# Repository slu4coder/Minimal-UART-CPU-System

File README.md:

# Legacy: Minimal UART CPU System

See https://github.com/slu4coder/Minimal-64x4-Home-Computer for the most recent version.

Quick note: This is a free and non-commercial project. I am in no way associated with any activies selling this as a product.
Any such activity represents a license violation. Individual licenses apply for hardware and software parts. Please refer to
appropriate documentations for detailed licensing information.

Minimal CPU 2.0 'Ultra' is now running at 10MHz(!) and may well be the fastest 8-bit general purpose 74HC logic breadboard computer to this date:

Latest PCB version 1.5:

● Build your own 'Minimal CPU System' on breadboards: https://www.youtube.com/watch?v=Gz1VVOsNn_8

● Python-like high-level programming language MIN released: https://www.youtube.com/watch?v=H342TwW4R7k

● 'Minimal VGA Extension Card' released! https://github.com/slu4coder/DIY-VideoRAM/tree/main/KiCAD

● 'Minimal CPU System' Emulator released! See user manual chapter 'Minimal Emulator' for details.

● Native assembler and text editor released!

● User Manual and Reference: https://docs.google.com/document/d/1c2ZHtLd1BBAwcBAjBZZJmCA3AXpbpv80dlAtsMYpuF4/edit?usp=sharing

● Revision 1.5 is out now featuring 512KB FLASH SSD, 3.6864MHz clock speed and an expansion port!
https://www.youtube.com/watch?v=osVi06VKvA0

● Minimal Python Assembler released: https://www.youtube.com/watch?v=rdKX9hzA2lU

● The Minimal CPU System now has a dedicated hardware serial 'Minimal Terminal': https://github.com/slu4coder/Minimal-Terminal
but can also be operated via a USB-to-serial breakout board and a terminal emulation (e. g. Tera Term) of cause.

I've built my own Computer from scratch - using nothing but TTL chips, because, well, why not? I wanted a CPU that is easy to understand, fun to build and powerful enough to allow for programming educational stuff and little games on it. Ah, and by the way - it should be as simple as possible - sort of the "Simplest Usable Personal Computer". This repo provides you with everything you need to follow my one-and-a-half-year journey down this rabbit hole. Besides running some video game classics, this little DIY CPU is capable of parsing arbitrary mathmatical expressions and performing floating point calculations in single (32-bit) precision. And it comes with an SSD file system, too, since it uses it's own FLASH IC as permanent SSD storage. Over the last year I have written an entire native toolchain: a text editor, an assembler and the Python-like high-level programming language MIN.

WHAT YOU GET:

  ● Block diagram of the CPU and overview it's instruction set
  
  ● KiCAD project files with detailed schematics and PCB layout
  
  ● Gerber files ready to be submitted at any PCB manufacturer of your choice
  
  ● Bill of material
  
  ● Images in .bin format of both the ROM and the CPU's control microcode
  
  ● Source code of the minimal operating system MinOS and several demos and games
  
  ● Cross-assembler 'asm.exe' running on Windows (or Python) to comfortably write, assemble and upload your own software

TECHNICAL SPECIFICATION:
  
  ● Processing power (1.0Mips @8.3MHz) comparable to 2.3 x Commodore 64 or Apple II
  
  ● Clear(est?) and simple(st? – you judge!) design for fun and education
  
  ● 8-bit data bus, 16-bit address bus, Von-Neumann architecture
  
  ● 64 instructions (conditional branching, subroutines, stack and word ops)
  
  ● 32KB RAM / 512KB FLASH ROM (OS, memory monitor, disassembler, tools)
  
  ● SSD file system (commands LOAD, SAVE, DIR, DELETE, FORMAT as you'd expect)
  
  ● UART interface (up to 500kbps) for terminal display, keyboard input and file I/O
 
  ● Expansion port (I/O card and VGA card available, build your own!)
   
  ● 24 (16) control signals, 2 registers A and B, ALU (arithmetic and logic unit) = simple adder, 3 flags (negative, carry and zero)
  
  ● Built from 74HCxx TTL logic on 120mm x 190mm PCB or 8 breadboards

I hope you find this information useful, educational or otherwise interesting. I'd love to hear about your build, so meet me on YouTube.

https://www.youtube.com/channel/UCXYQcMpUBT3aaQKfmAVJNow

Have fun!
slu4

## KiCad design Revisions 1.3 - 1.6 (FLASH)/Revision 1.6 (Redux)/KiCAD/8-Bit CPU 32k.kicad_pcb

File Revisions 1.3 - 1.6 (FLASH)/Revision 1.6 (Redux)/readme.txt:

Revision 1.6 ("Redux") is software-compatible to revision 1.5. The schematics and the microcode, however, have been optimized for build-simplicity on breadboards. Only 39 ICs are being used, compared to the 47 ICs of revision 1.5.

NEW: Minimal 'Beast Mode' can run at up to 8.3MHz clock speed.

ONLY USE HIGH-QUALITY BREADBOARDS FOR YOUR BUILD!

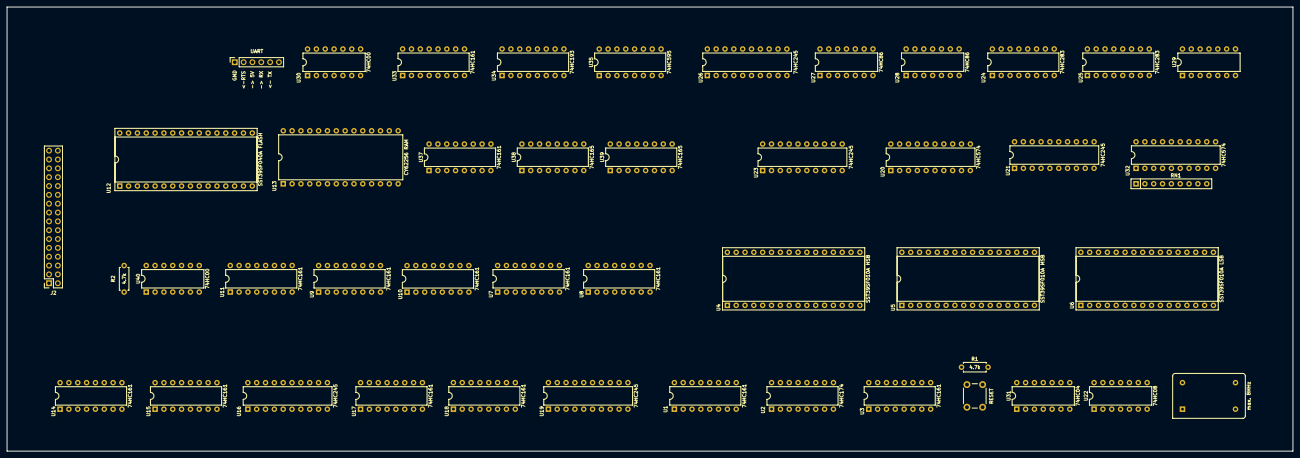
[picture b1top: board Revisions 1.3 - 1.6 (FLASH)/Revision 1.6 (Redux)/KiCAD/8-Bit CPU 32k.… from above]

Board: 2 copper layers, 369.6 x 127.6 mm, 46 parts (0 on the bottom side), 150 nets, no tracks yet.

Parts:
J1: UART; PinSocket_1x06_P2.54mm_Vertical
J2: EXPANSION PORT; PinSocket_2x16_P2.54mm_Vertical
R1, R2: 4.7k; R_Axial_DIN0207_L6.3mm_D2.5mm_P7.62mm_Horizontal
RN1: 470; R_Array_SIP9
SW1: RESET; SW_PUSH_6mm
U1, U3, U7, U8, U9, U10, U11, U14, U15, U17, U18, U33, U37: 74HC161; DIP-16_W7.62mm
U2: 74HC174; DIP-16_W7.62mm
U4: SST39SF010A HSB; DIP-32_W15.24mm_Socket
U5: SST39SF010A MSB; DIP-32_W15.24mm_Socket
U6: SST39SF010A LSB; DIP-32_W15.24mm_Socket
U12: SST39SF040A FLASH; DIP-32_W15.24mm_Socket
U13: CY62256 RAM; DIP-28_W15.24mm
U16, U19, U21, U23, U26: 74HC245; DIP-20_W7.62mm
U20, U32: 74HC574; DIP-20_W7.62mm
U22: 74HC08; DIP-14_W7.62mm
U24, U25: 74HC283; DIP-16_W7.62mm
U27, U28: 74HC86; DIP-14_W7.62mm
U29: 74HC4078; DIP-14_W7.62mm
U30, U40: 74HC00; DIP-14_W7.62mm
U31: 74HC04; DIP-14_W7.62mm
U34: 74HC193; DIP-16_W7.62mm
U35: 74HC595; DIP-16_W7.62mm
U38, U39: 74HC165; DIP-16_W7.62mm
X1: max. 8MHz; Oscillator_DIP-14

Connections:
+5V: J1.3, J2.3, R1.1, R2.2, RN1.1 (common), U1.1 (~MR), U1.16 (VCC), U2.1 (~Mr), U2.16 (VCC), U3.7 (CEP), U3.10 (CET), U3.16 (VCC), U4.31 (~WE), U4.32 (VCC), U5.31 (~WE), U5.32 (VCC), U6.31 (~WE), U6.32 (VCC), U7.1 (~MR), U7.16 (VCC), U8.1 (~MR), U8.16 (VCC), U9.1 (~MR), U9.16 (VCC), U10.1 (~MR), U10.16 (VCC), U11.16 (VCC), U12.32 (VCC), U13.28 (VCC), U14.16 (VCC), U15.16 (VCC), U16.20 (VCC), U17.16 (VCC), U18.16 (VCC), U19.20 (VCC), U20.20 (VCC), U21.20 (VCC), U22.14 (VCC), U23.20 (VCC), U24.16 (VCC), U25.16 (VCC), U26.20 (VCC), U27.14 (VCC), U28.14 (VCC), U29.7 (GND), U30.14 (VCC), U31.14 (VCC), U32.20 (VCC), U33.7 (CEP), U33.9 (~PE), U33.16 (VCC), U34.1 (D1), U34.5 (CPU), U34.9 (D3), U34.16 (VCC), U35.10 (~SRCLR), U35.16 (VCC), U37.7 (CEP), U37.9 (~PE), U37.10 (CET), U37.16 (VCC), U38.6 (D7), U38.16 (VCC), U39.3 (D4), U39.4 (D5), U39.10 (DS), U39.11 (D0), U39.12 (D1), U39.13 (D2), U39.14 (D3), U39.16 (VCC), U40.14 (VCC), X1.14 (Vcc)
/ALU/A0: U21.18 (B0), U24.5 (A1), U32.19 (Q0)
/ALU/A1: U21.17 (B1), U24.3 (A2), U32.18 (Q1)
/ALU/A2: U21.16 (B2), U24.14 (A3), U32.17 (Q2)
/ALU/A3: U21.15 (B3), U24.12 (A4), U32.16 (Q3)
/ALU/A4: U21.14 (B4), U25.5 (A1), U32.15 (Q4)
/ALU/A5: U21.13 (B5), U25.3 (A2), U32.14 (Q5)
/ALU/A6: U21.12 (B6), U25.14 (A3), U32.13 (Q6)
/ALU/A7: U21.11 (B7), U25.12 (A4), U32.12 (Q7)
/ALU/B0: U20.19 (Q0), U23.18 (B0), U27.13
/ALU/B1: U20.18 (Q1), U23.17 (B1), U27.10
/ALU/B2: U20.17 (Q2), U23.16 (B2), U27.2
/ALU/B3: U20.16 (Q3), U23.15 (B3), U27.5
/ALU/B4: U20.15 (Q4), U23.14 (B4), U28.13
/ALU/B5: U20.14 (Q5), U23.13 (B5), U28.10
/ALU/B6: U20.13 (Q6), U23.12 (B6), U28.2
/ALU/B7: U20.12 (Q7), U23.11 (B7), U28.5
/ALU/BUS0: J2.9, RN1.2 (R1), U2.3 (D0), U7.3 (D0), U9.3 (D0), U11.3 (D0), U12.13 (I/O0), U13.11 (I/O0), U14.3 (D0), U16.2 (A0), U17.3 (D0), U19.2 (A0), U20.2 (D0), U21.2 (A0), U23.2 (A0), U26.2 (A0), U32.2 (D0), U35.7 (QH), U38.4 (D5)
/ALU/BUS1: J2.10, RN1.3 (R2), U2.4 (D1), U7.4 (D1), U9.4 (D1), U11.4 (D1), U12.14 (I/O1), U13.12 (I/O1), U14.4 (D1), U16.3 (A1), U17.4 (D1), U19.3 (A1), U20.3 (D1), U21.3 (A1), U23.3 (A1), U26.3 (A1), U32.3 (D1), U35.6 (QG), U38.3 (D4)
/ALU/BUS2: J2.11, RN1.4 (R3), U2.6 (D2), U7.5 (D2), U9.5 (D2), U11.5 (D2), U12.15 (I/O2), U13.13 (I/O2), U14.5 (D2), U16.4 (A2), U17.5 (D2), U19.4 (A2), U20.4 (D2), U21.4 (A2), U23.4 (A2), U26.4 (A2), U32.4 (D2), U35.5 (QF), U38.14 (D3)
/ALU/BUS3: J2.12, RN1.5 (R4), U2.11 (D3), U7.6 (D3), U9.6 (D3), U11.6 (D3), U12.17 (I/O3), U13.15 (I/O3), U14.6 (D3), U16.5 (A3), U17.6 (D3), U19.5 (A3), U20.5 (D3), U21.5 (A3), U23.5 (A3), U26.5 (A3), U32.5 (D3), U35.4 (QE), U38.13 (D2)
/ALU/BUS4: J2.13, RN1.6 (R5), U2.13 (D4), U8.3 (D0), U10.3 (D0), U12.18 (I/O4), U13.16 (I/O4), U15.3 (D0), U16.6 (A4), U18.3 (D0), U19.6 (A4), U20.6 (D4), U21.6 (A4), U23.6 (A4), U26.6 (A4), U32.6 (D4), U35.3 (QD), U38.12 (D1)
/ALU/BUS5: J2.14, RN1.7 (R6), U2.14 (D5), U8.4 (D1), U10.4 (D1), U12.19 (I/O5), U13.17 (I/O5), U15.4 (D1), U16.7 (A5), U18.4 (D1), U19.7 (A5), U20.7 (D5), U21.7 (A5), U23.7 (A5), U26.7 (A5), U32.7 (D5), U35.2 (QC), U38.11 (D0)
/ALU/BUS6: J2.15, RN1.8 (R7), U8.5 (D2), U10.5 (D2), U12.20 (I/O6), U13.18 (I/O6), U15.5 (D2), U16.8 (A6), U18.5 (D2), U19.8 (A6), U20.8 (D6), U21.8 (A6), U23.8 (A6), U26.8 (A6), U32.8 (D6), U35.1 (QB), U39.6 (D7)
/ALU/BUS7: J2.16, RN1.9 (R8), U8.6 (D3), U10.6 (D3), U12.21 (I/O7), U13.19 (I/O7), U15.6 (D3), U16.9 (A7), U18.6 (D3), U19.9 (A7), U20.9 (D7), U21.9 (A7), U23.9 (A7), U26.9 (A7), U32.9 (D7), U35.15 (QA), U39.5 (D6)
/ALU/EC: U6.15 (I/O2), U24.7 (C0)
/ALU/ES: U6.14 (I/O1), U27.1, U27.4, U27.9, U27.12, U28.1, U28.4, U28.9, U28.12
/ALU/FLAG_C: U1.4 (D1), U25.9 (C4)
/ALU/FLAG_N: U1.5 (D2), U25.10 (S4), U26.11 (B7), U29.2
/ALU/FLAG_Z: U1.3 (D0), U29.13
/ALU/~EO: U6.13 (I/O0), U26.19 (CE)
/Control Logic/AI: U6.17 (I/O3), U22.9
/Control Logic/BI: U6.19 (I/O5), U22.12
/Control Logic/BUSY: U1.6 (D3), U33.10 (CET), U34.13 (~TCD)
/Control Logic/CE: U5.21 (I/O7), U14.7 (CEP), U14.10 (CET), U15.7 (CEP), U17.7 (CEP), U18.7 (CEP)
/Control Logic/Flag0: U1.14 (Q0), U4.23 (A10), U5.23 (A10), U6.23 (A10)
/Control Logic/Flag1: U1.13 (Q1), U4.25 (A11), U5.25 (A11), U6.25 (A11)
/Control Logic/Flag2: U1.12 (Q2), U4.4 (A12), U5.4 (A12), U6.4 (A12)
/Control Logic/Flag3: U1.11 (Q3), U4.28 (A13), U5.28 (A13), U6.28 (A13)
/Control Logic/II: U6.21 (I/O7), U22.5
/Control Logic/Inst0: U2.2 (Q0), U4.8 (A4), U5.8 (A4), U6.8 (A4)
/Control Logic/Inst1: U2.5 (Q1), U4.7 (A5), U5.7 (A5), U6.7 (A5)
/Control Logic/Inst2: U2.7 (Q2), U4.6 (A6), U5.6 (A6), U6.6 (A6)
/Control Logic/Inst3: U2.10 (Q3), U4.5 (A7), U5.5 (A7), U6.5 (A7)
/Control Logic/Inst4: U2.12 (Q4), U4.27 (A8), U5.27 (A8), U6.27 (A8)
/Control Logic/Inst5: U2.15 (Q5), U4.26 (A9), U5.26 (A9), U6.26 (A9)
/Control Logic/ME: U4.13 (I/O0), U7.7 (CEP), U7.10 (CET), U8.7 (CEP), U9.7 (CEP), U10.7 (CEP)
/Control Logic/RI: J2.6, U4.20 (I/O6), U40.9
/Control Logic/Step0: U3.14 (Q0), U4.12 (A0), U5.12 (A0), U6.12 (A0)
/Control Logic/Step1: U3.13 (Q1), U4.11 (A1), U5.11 (A1), U6.11 (A1)
/Control Logic/Step2: U3.12 (Q2), U4.10 (A2), U5.10 (A2), U6.10 (A2)
/Control Logic/Step3: U3.11 (Q3), U4.9 (A3), U5.9 (A3), U6.9 (A3)
/Control Logic/TI: U4.17 (I/O3), U30.9
/Control Logic/~AO: U6.18 (I/O4), U21.19 (CE)
/Control Logic/~BO: U6.20 (I/O6), U23.19 (CE)
/Control Logic/~CIH: U5.18 (I/O4), U17.9 (~PE), U18.9 (~PE)
/Control Logic/~CIL: U5.17 (I/O3), U14.9 (~PE), U15.9 (~PE)
/Control Logic/~COH: U5.20 (I/O6), U19.19 (CE)
/Control Logic/~COL: U5.19 (I/O5), U16.19 (CE)
/Control Logic/~FI: U1.9 (~PE), U5.14 (I/O1)
/Control Logic/~IC: U3.1 (~MR), U5.15 (I/O2)
/Control Logic/~KI: U5.13 (I/O0), U11.9 (~PE)
/Control Logic/~MIH: U4.15 (I/O2), U9.9 (~PE), U10.9 (~PE)
/Control Logic/~MIL: U4.14 (I/O1), U7.9 (~PE), U8.9 (~PE)
/Control Logic/~RO: J2.7, U4.21 (I/O7), U12.24 (~OE), U13.22 (~OE)
/Control Logic/~TO: U4.18 (I/O4), U30.5, U35.13 (~OE)
/Memory/BANK0: U11.14 (Q0), U12.3 (A15)
/Memory/BANK1: U11.13 (Q1), U12.2 (A16)
/Memory/BANK2: U11.12 (Q2), U12.30 (A17)
/Memory/BANK3: U11.11 (Q3), U12.1 (A18)
/Memory/M0: J2.17, U7.14 (Q0), U12.12 (A0), U13.21 (A0)
/Memory/M1: J2.18, U7.13 (Q1), U12.11 (A1), U13.23 (A1)
/Memory/M2: J2.19, U7.12 (Q2), U12.10 (A2), U13.24 (A2)
/Memory/M3: J2.20, U7.11 (Q3), U12.9 (A3), U13.25 (A3)
/Memory/M4: J2.21, U8.14 (Q0), U12.8 (A4), U13.26 (A4)
/Memory/M5: J2.22, U8.13 (Q1), U12.7 (A5), U13.1 (A5)
/Memory/M6: J2.23, U8.12 (Q2), U12.6 (A6), U13.2 (A6)
/Memory/M7: J2.24, U8.11 (Q3), U12.5 (A7), U13.3 (A7)
/Memory/M8: J2.25, U9.14 (Q0), U12.27 (A8), U13.4 (A8)
/Memory/M9: J2.26, U9.13 (Q1), U12.26 (A9), U13.5 (A9)
/Memory/M10: J2.27, U9.12 (Q2), U12.23 (A10), U13.6 (A10)
/Memory/M11: J2.28, U9.11 (Q3), U12.25 (A11), U13.7 (A11)
/Memory/M12: J2.29, U10.14 (Q0), U12.4 (A12), U13.8 (A12)
/Memory/M13: J2.30, U10.13 (Q1), U12.28 (A13), U13.9 (A13)
/Memory/M14: J2.31, U10.12 (Q2), U12.29 (A14), U13.10 (A14)
/Memory/M15: J2.32, U10.11 (Q3), U40.1, U40.12, U40.13
/Memory/~INH: J2.8, R2.1, U40.2, U40.4
/UART Receiver/RTS: J1.2, U30.3, U30.4, U33.1 (~MR), U34.11 (~PL)
/UART Receiver/RX: J1.4, U30.1, U35.14 (SER)
/UART Transmitter/TX: J1.5, U38.9 (Q7)
CLOCK0: U1.2 (CP), U3.2 (CP), U22.1, U31.1, X1.8 (OUT)
CLOCK1: U14.2 (CP), U15.2 (CP), U17.2 (CP), U18.2 (CP), U31.4, U31.5
CLOCK2: J2.5, U11.2 (CP), U31.8, U31.11, U33.2 (CP), U37.2 (CP)
CLOCK3: U7.2 (CP), U8.2 (CP), U9.2 (CP), U10.2 (CP), U31.12
GND: J1.1, J2.1, SW1.1, U1.7 (CEP), U1.8 (GND), U1.10 (CET), U2.8 (GND), U3.3 (D0), U3.4 (D1), U3.5 (D2), U3.6 (D3), U3.8 (GND), U4.2 (A16), U4.3 (A15), U4.16 (GND), U4.22 (~CE), U4.24 (~OE), U4.29 (A14), U5.2 (A16), U5.3 (A15), U5.16 (GND), U5.22 (~CE), U5.24 (~OE), U5.29 (A14), U6.2 (A16), U6.3 (A15), U6.16 (GND), U6.22 (~CE), U6.24 (~OE), U6.29 (A14), U7.8 (GND), U8.8 (GND), U9.8 (GND), U10.8 (GND), U11.7 (CEP), U11.8 (GND), U11.10 (CET), U12.16 (GND), U13.14 (GND), U14.8 (GND), U15.8 (GND), U16.1 (A->B), U16.10 (GND), U17.8 (GND), U18.8 (GND), U19.1 (A->B), U19.10 (GND), U20.1 (OE), U20.10 (GND), U21.1 (A->B), U21.10 (GND), U22.7 (GND), U23.1 (A->B), U23.10 (GND), U24.8 (GND), U25.8 (GND), U26.1 (A->B), U26.10 (GND), U27.7 (GND), U28.7 (GND), U29.14 (VCC), U30.7 (GND), U30.12, U30.13, U31.7 (GND), U32.1 (OE), U32.10 (GND), U33.3 (D0), U33.4 (D1), U33.5 (D2), U33.6 (D3), U33.8 (GND), U34.8 (GND), U34.10 (D2), U34.14 (MR), U34.15 (D0), U35.8 (GND), U37.3 (D0), U37.4 (D1), U37.5 (D2), U37.6 (D3), U37.8 (GND), U38.5 (D6), U38.8 (GND), U38.15 (~CE), U39.8 (GND), U39.15 (~CE), U40.7 (GND), X1.7 (GND)
unnamed: U2.9 (Cp), U22.6
unnamed: U7.15 (TC), U8.10 (CET)
unnamed: U8.15 (TC), U9.10 (CET)
unnamed: U9.15 (TC), U10.10 (CET)
unnamed: U12.22 (~CE), U40.6
unnamed: U12.31 (~WE), U13.27 (~WE), U40.8
unnamed: U13.20 (~CE), U40.3
unnamed: U14.11 (Q3), U16.15 (B3)
unnamed: U14.12 (Q2), U16.16 (B2)
unnamed: U14.13 (Q1), U16.17 (B1)
unnamed: U14.14 (Q0), U16.18 (B0)
unnamed: U14.15 (TC), U15.10 (CET)
unnamed: U15.11 (Q3), U16.11 (B7)
unnamed: U15.12 (Q2), U16.12 (B6)
unnamed: U15.13 (Q1), U16.13 (B5)
unnamed: U15.14 (Q0), U16.14 (B4)
unnamed: U15.15 (TC), U17.10 (CET)
unnamed: U17.11 (Q3), U19.15 (B3)
unnamed: U17.12 (Q2), U19.16 (B2)
unnamed: U17.13 (Q1), U19.17 (B1)
unnamed: U17.14 (Q0), U19.18 (B0)
unnamed: U17.15 (TC), U18.10 (CET)
unnamed: U18.11 (Q3), U19.11 (B7)
unnamed: U18.12 (Q2), U19.12 (B6)
unnamed: U18.13 (Q1), U19.13 (B5)
unnamed: U18.14 (Q0), U19.14 (B4)
unnamed: U20.11 (Cp), U22.11
unnamed: U22.2, U31.10, U31.13
unnamed: U22.8, U32.11 (Cp)
unnamed: U24.1 (S2), U26.17 (B1), U29.11
unnamed: U24.2 (B2), U27.8
unnamed: U24.4 (S1), U26.18 (B0), U29.12
unnamed: U24.6 (B1), U27.11
unnamed: U24.9 (C4), U25.7 (C0)
unnamed: U24.10 (S4), U26.15 (B3), U29.9
unnamed: U24.11 (B4), U27.6
unnamed: U24.13 (S3), U26.16 (B2), U29.10
unnamed: U24.15 (B3), U27.3
unnamed: U25.1 (S2), U26.13 (B5), U29.4
unnamed: U25.2 (B2), U28.8
unnamed: U25.4 (S1), U26.14 (B4), U29.5
unnamed: U25.6 (B1), U28.11
unnamed: U25.11 (B4), U28.6
unnamed: U25.13 (S3), U26.12 (B6), U29.3
unnamed: U25.15 (B3), U28.3
unnamed: U30.2, U30.6
unnamed: U30.8, U37.1 (~MR), U38.1 (~PL), U39.1 (~PL)
unnamed: U31.2, U31.3
unnamed: U31.6, U31.9
unnamed: U33.11 (Q3), U34.4 (CPD), U35.11 (SRCLK), U35.12 (RCLK)
unnamed: U37.11 (Q3), U38.2 (CP), U39.2 (CP)
unnamed: U38.10 (DS), U39.9 (Q7)
unnamed: U40.5, U40.11
PULSE: J2.2, U22.3, U22.4, U22.13, U30.10, U40.10
~RESET: J2.4, R1.2, SW1.2, U3.9 (~PE), U11.1 (~MR), U14.1 (~MR), U15.1 (~MR), U17.1 (~MR), U18.1 (~MR)

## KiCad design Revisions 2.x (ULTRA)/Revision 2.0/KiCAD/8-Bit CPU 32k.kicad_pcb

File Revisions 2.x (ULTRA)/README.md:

# Breadboard version 2.0 (Experimental)

Experimental evolutionary revision of my Minimal UART CPU, exploring the idea of efficient PC-to-MAR transfer.
My later Minimal 64x4 TTL computer uses a better approach.

ONLY USE HIGH-QUALITY BREADBOARDS FOR YOUR BUILD!

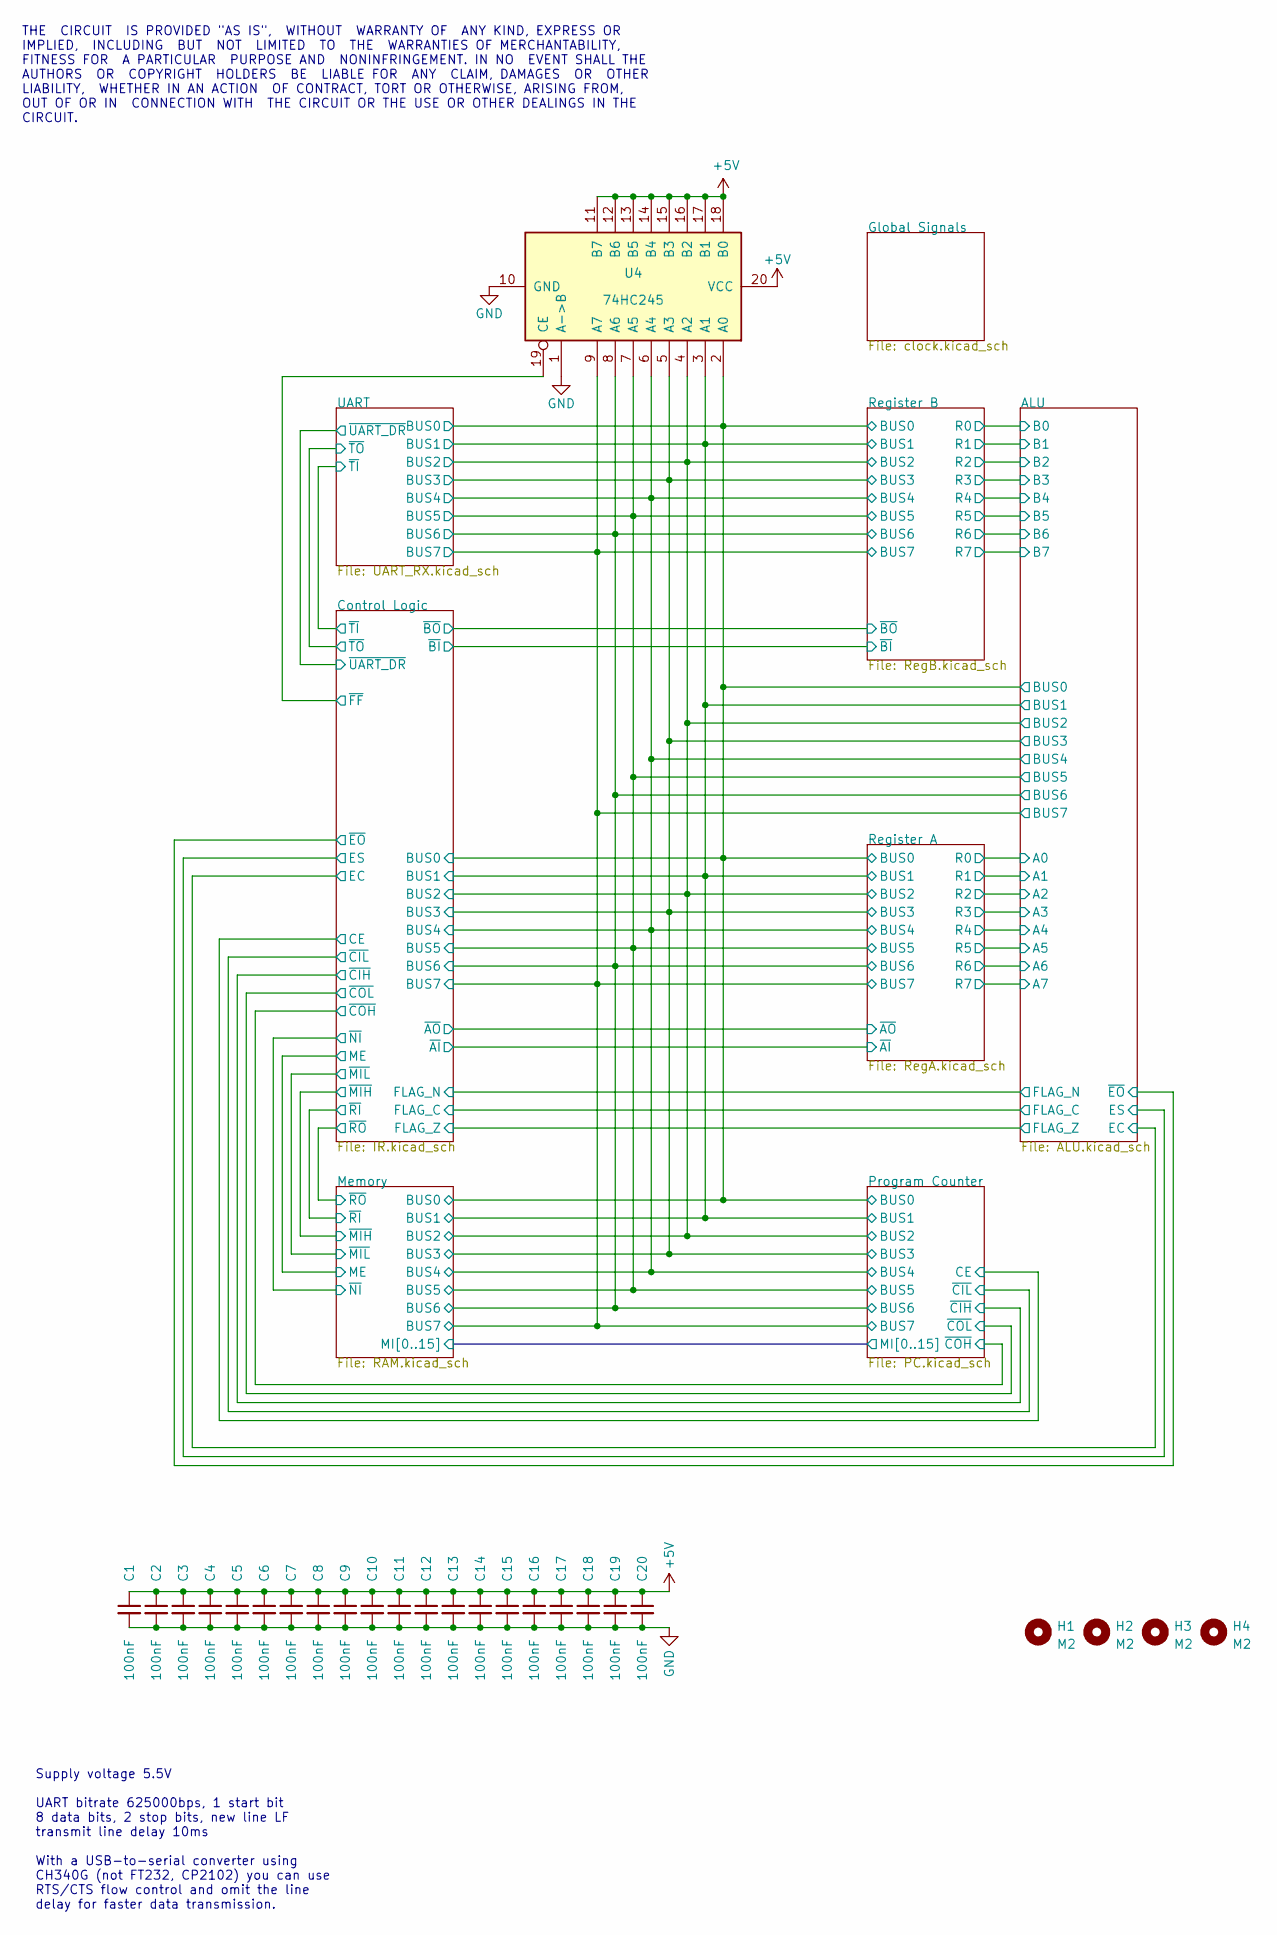
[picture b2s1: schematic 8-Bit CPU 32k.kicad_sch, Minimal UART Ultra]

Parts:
C1, C2, C3, C4, C5, C6, C7, C8, C9, C10, C11, C12, C13, C14, C15, C16, C17, C18, C19, C20: 100nF; C_Disc_D3.4mm_W2.1mm_P2.50mm
H1, H2, H3, H4: M2; MountingHole_2.2mm_M2
U4: 74HC245; DIP-20_W7.62mm

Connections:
+5V: C1.1, C2.1, C3.1, C4.1, C5.1, C6.1, C7.1, C8.1, C9.1, C10.1, C11.1, C12.1, C13.1, C14.1, C15.1, C16.1, C17.1, C18.1, C19.1, C20.1, U4.11 (B7), U4.12 (B6), U4.13 (B5), U4.14 (B4), U4.15 (B3), U4.16 (B2), U4.17 (B1), U4.18 (B0), U4.20 (VCC); also elsewhere on the board
/ALU/BUS0: U4.2 (A0); also elsewhere on the board
/ALU/BUS1: U4.3 (A1); also elsewhere on the board
/ALU/BUS2: U4.4 (A2); also elsewhere on the board
/ALU/BUS3: U4.5 (A3); also elsewhere on the board
/ALU/BUS4: U4.6 (A4); also elsewhere on the board
/ALU/BUS5: U4.7 (A5); also elsewhere on the board
/ALU/BUS6: U4.8 (A6); also elsewhere on the board
/ALU/BUS7: U4.9 (A7); also elsewhere on the board
/Control Logic/~FF: U4.19 (CE); also elsewhere on the board
GND: C1.2, C2.2, C3.2, C4.2, C5.2, C6.2, C7.2, C8.2, C9.2, C10.2, C11.2, C12.2, C13.2, C14.2, C15.2, C16.2, C17.2, C18.2, C19.2, C20.2, U4.1 (A->B), U4.10 (GND); also elsewhere on the board

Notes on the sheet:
Supply voltage 5.5V UART bitrate 625000bps, 1 start bit 8 data bits, 2 stop bits, new line LF transmit line delay 10ms With a USB-to-serial converter using CH340G (not FT232, CP2102) you can use RTS/CTS flow control and omit the line delay for faster data transmission.
THE CIRCUIT IS PROVIDED "AS IS", WITHOUT WARRANTY OF ANY KIND, EXPRESS OR IMPLIED, INCLUDING BUT NOT LIMITED TO THE WARRANTIES OF MERCHANTABILITY, FITNESS FOR A PARTICULAR PURPOSE AND NONINFRINGEMENT. IN NO EVENT SHALL THE AUTHORS OR COPYRIGHT HOLDERS BE LIABLE FOR ANY CLAIM, DAMAGES OR OTHER LIABI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

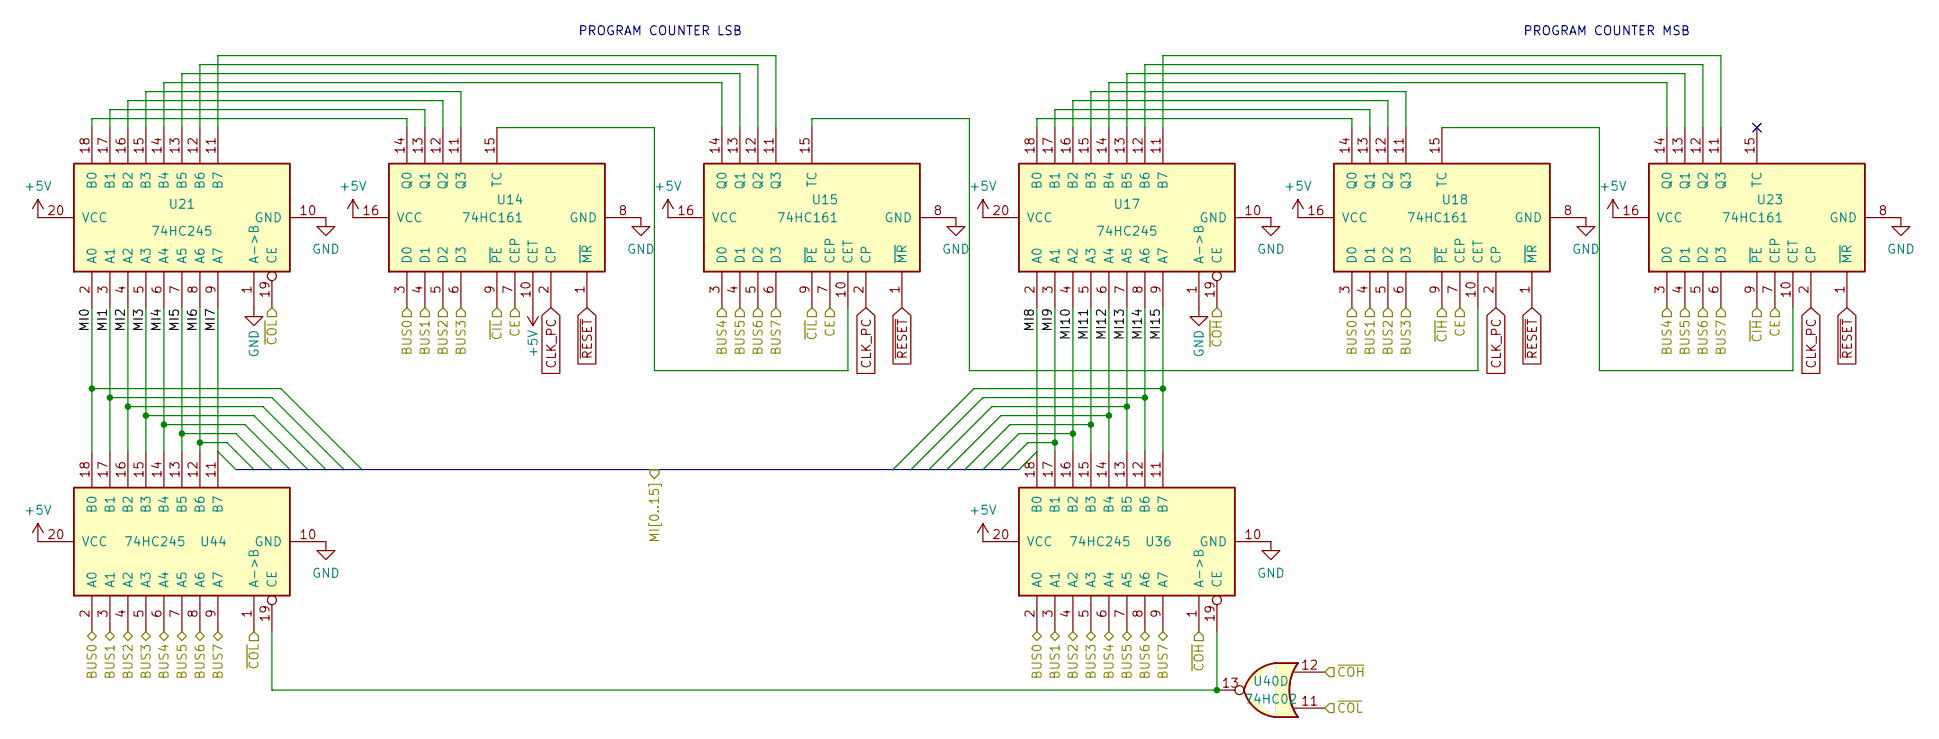
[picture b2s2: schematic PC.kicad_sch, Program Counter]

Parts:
U14, U15, U18, U23: 74HC161; DIP-16_W7.62mm
U17, U21, U36, U44: 74HC245; DIP-20_W7.62mm
U40: 74HC02; DIP-14_W7.62mm

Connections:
+5V: U14.10 (CET), U14.16 (VCC), U15.16 (VCC), U17.20 (VCC), U18.16 (VCC), U21.20 (VCC), U23.16 (VCC), U36.20 (VCC), U44.20 (VCC); also elsewhere on the board
/ALU/BUS0: U14.3 (D0), U18.3 (D0), U36.2 (A0), U44.2 (A0); also elsewhere on the board
/ALU/BUS1: U14.4 (D1), U18.4 (D1), U36.3 (A1), U44.3 (A1); also elsewhere on the board
/ALU/BUS2: U14.5 (D2), U18.5 (D2), U36.4 (A2), U44.4 (A2); also elsewhere on the board
/ALU/BUS3: U14.6 (D3), U18.6 (D3), U36.5 (A3), U44.5 (A3); also elsewhere on the board
/ALU/BUS4: U15.3 (D0), U23.3 (D0), U36.6 (A4), U44.6 (A4); also elsewhere on the board
/ALU/BUS5: U15.4 (D1), U23.4 (D1), U36.7 (A5), U44.7 (A5); also elsewhere on the board
/ALU/BUS6: U15.5 (D2), U23.5 (D2), U36.8 (A6), U44.8 (A6); also elsewhere on the board
/ALU/BUS7: U15.6 (D3), U23.6 (D3), U36.9 (A7), U44.9 (A7); also elsewhere on the board
/Control Logic/CE: U14.7 (CEP), U15.7 (CEP), U18.7 (CEP), U23.7 (CEP); also elsewhere on the board
/Control Logic/~CIH: U18.9 (~PE), U23.9 (~PE); also elsewhere on the board
/Control Logic/~CIL: U14.9 (~PE), U15.9 (~PE); also elsewhere on the board
/Control Logic/~COH: U17.19 (CE), U36.1 (A->B), U40.12; also elsewhere on the board
/Control Logic/~COL: U21.19 (CE), U40.11, U44.1 (A->B); also elsewhere on the board
/Memory/MI0: U21.2 (A0), U44.18 (B0); also elsewhere on the board
/Memory/MI1: U21.3 (A1), U44.17 (B1); also elsewhere on the board
/Memory/MI2: U21.4 (A2), U44.16 (B2); also elsewhere on the board
/Memory/MI3: U21.5 (A3), U44.15 (B3); also elsewhere on the board
/Memory/MI4: U21.6 (A4), U44.14 (B4); also elsewhere on the board
/Memory/MI5: U21.7 (A5), U44.13 (B5); also elsewhere on the board
/Memory/MI6: U21.8 (A6), U44.12 (B6); also elsewhere on the board
/Memory/MI7: U21.9 (A7), U44.11 (B7); also elsewhere on the board
/Memory/MI8: U17.2 (A0), U36.18 (B0); also elsewhere on the board
/Memory/MI9: U17.3 (A1), U36.17 (B1); also elsewhere on the board
/Memory/MI10: U17.4 (A2), U36.16 (B2); also elsewhere on the board
/Memory/MI11: U17.5 (A3), U36.15 (B3); also elsewhere on the board
/Memory/MI12: U17.6 (A4), U36.14 (B4); also elsewhere on the board
/Memory/MI13: U17.7 (A5), U36.13 (B5); also elsewhere on the board
/Memory/MI14: U17.8 (A6), U36.12 (B6); also elsewhere on the board
/Memory/MI15: U17.9 (A7), U36.11 (B7); also elsewhere on the board
CLK_PC: U14.2 (CP), U15.2 (CP), U18.2 (CP), U23.2 (CP); also elsewhere on the board
GND: U14.8 (GND), U15.8 (GND), U17.1 (A->B), U17.10 (GND), U18.8 (GND), U21.1 (A->B), U21.10 (GND), U23.8 (GND), U36.10 (GND), U44.10 (GND); also elsewhere on the board
unnamed: U14.11 (Q3), U21.15 (B3)
unnamed: U14.12 (Q2), U21.16 (B2)
unnamed: U14.13 (Q1), U21.17 (B1)
unnamed: U14.14 (Q0), U21.18 (B0)
unnamed: U14.15 (TC), U15.10 (CET)
unnamed: U15.11 (Q3), U21.11 (B7)
unnamed: U15.12 (Q2), U21.12 (B6)
unnamed: U15.13 (Q1), U21.13 (B5)
unnamed: U15.14 (Q0), U21.14 (B4)
unnamed: U15.15 (TC), U18.10 (CET)
unnamed: U17.11 (B7), U23.11 (Q3)
unnamed: U17.12 (B6), U23.12 (Q2)
unnamed: U17.13 (B5), U23.13 (Q1)
unnamed: U17.14 (B4), U23.14 (Q0)
unnamed: U17.15 (B3), U18.11 (Q3)
unnamed: U17.16 (B2), U18.12 (Q2)
unnamed: U17.17 (B1), U18.13 (Q1)
unnamed: U17.18 (B0), U18.14 (Q0)
unnamed: U18.15 (TC), U23.10 (CET)
unnamed: U36.19 (CE), U40.13, U44.19 (CE)
~RESET: U14.1 (~MR), U15.1 (~MR), U18.1 (~MR), U23.1 (~MR); also elsewhere on the board

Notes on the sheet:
PROGRAM COUNTER MSB
PROGRAM COUNTER LSB

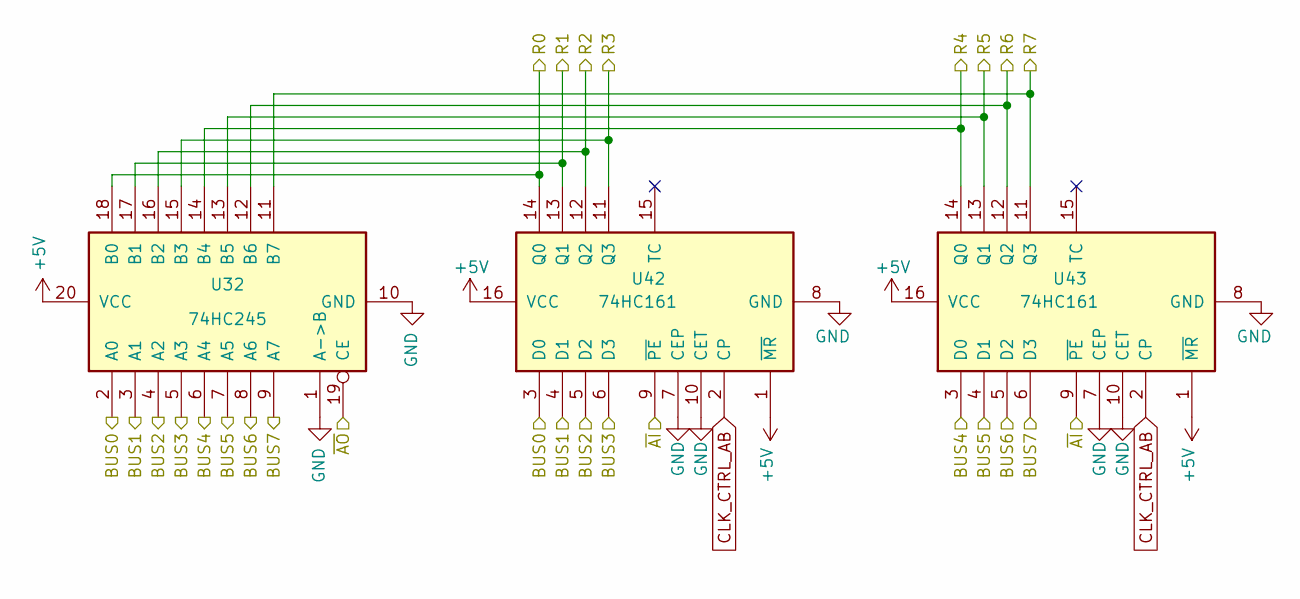
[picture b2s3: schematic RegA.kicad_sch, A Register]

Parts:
U32: 74HC245; DIP-20_W7.62mm
U42, U43: 74HC161; DIP-16_W7.62mm

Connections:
+5V: U32.20 (VCC), U42.1 (~MR), U42.16 (VCC), U43.1 (~MR), U43.16 (VCC); also elsewhere on the board
/ALU/A0: U32.18 (B0), U42.14 (Q0); also elsewhere on the board
/ALU/A1: U32.17 (B1), U42.13 (Q1); also elsewhere on the board
/ALU/A2: U32.16 (B2), U42.12 (Q2); also elsewhere on the board
/ALU/A3: U32.15 (B3), U42.11 (Q3); also elsewhere on the board
/ALU/A4: U32.14 (B4), U43.14 (Q0); also elsewhere on the board
/ALU/A5: U32.13 (B5), U43.13 (Q1); also elsewhere on the board
/ALU/A6: U32.12 (B6), U43.12 (Q2); also elsewhere on the board
/ALU/A7: U32.11 (B7), U43.11 (Q3); also elsewhere on the board
/ALU/BUS0: U32.2 (A0), U42.3 (D0); also elsewhere on the board
/ALU/BUS1: U32.3 (A1), U42.4 (D1); also elsewhere on the board
/ALU/BUS2: U32.4 (A2), U42.5 (D2); also elsewhere on the board
/ALU/BUS3: U32.5 (A3), U42.6 (D3); also elsewhere on the board
/ALU/BUS4: U32.6 (A4), U43.3 (D0); also elsewhere on the board
/ALU/BUS5: U32.7 (A5), U43.4 (D1); also elsewhere on the board
/ALU/BUS6: U32.8 (A6), U43.5 (D2); also elsewhere on the board
/ALU/BUS7: U32.9 (A7), U43.6 (D3); also elsewhere on the board
/Control Logic/~AI: U42.9 (~PE), U43.9 (~PE); also elsewhere on the board
/Control Logic/~AO: U32.19 (CE); also elsewhere on the board
CLK_CTRL_AB: U42.2 (CP), U43.2 (CP); also elsewhere on the board
GND: U32.1 (A->B), U32.10 (GND), U42.7 (CEP), U42.8 (GND), U42.10 (CET), U43.7 (CEP), U43.8 (GND), U43.10 (CET); also elsewhere on the board

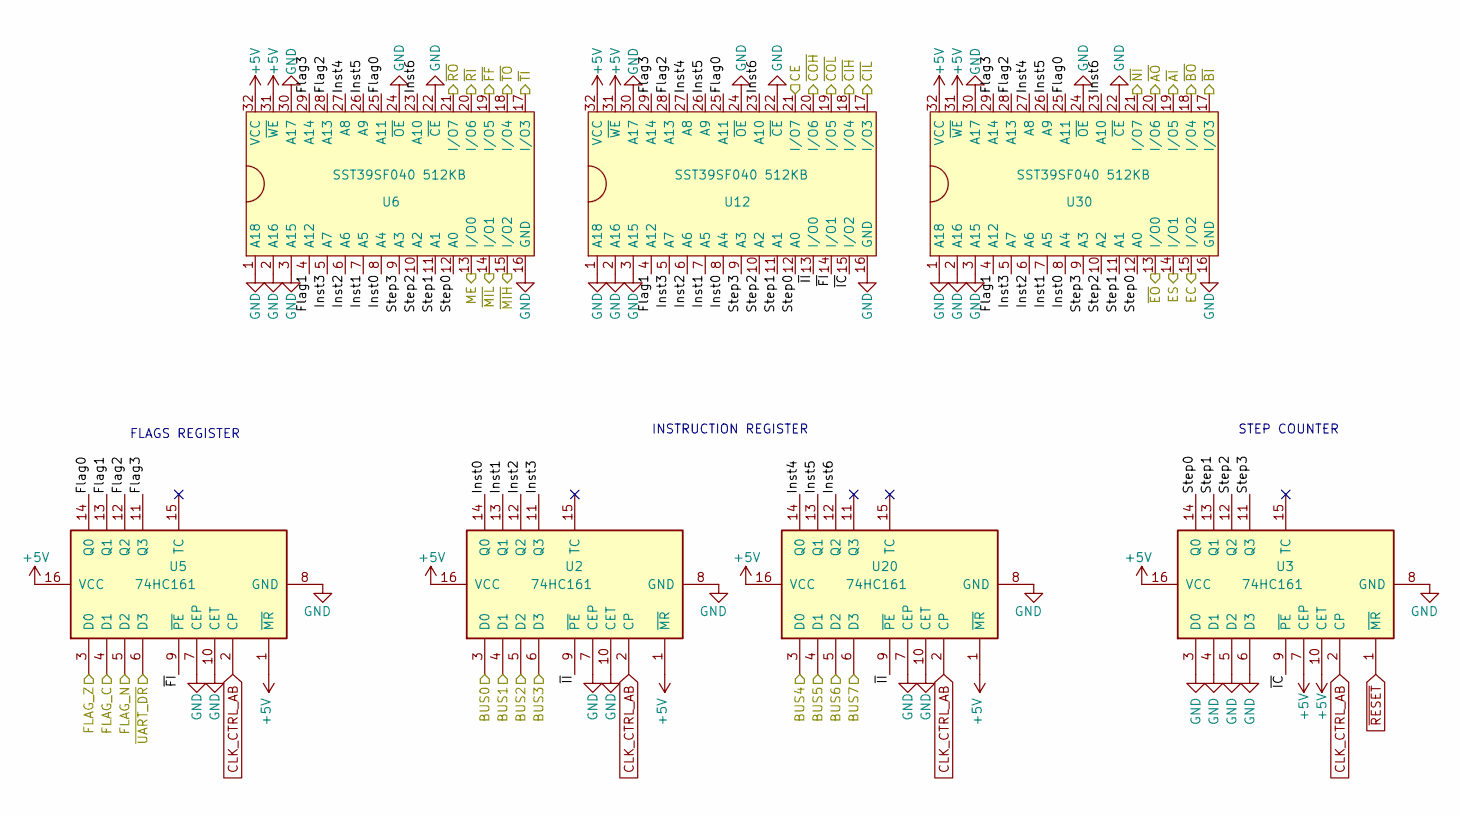
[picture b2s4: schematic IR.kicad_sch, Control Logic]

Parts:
U2, U3, U5, U20: 74HC161; DIP-16_W7.62mm
U6, U12, U30: SST39SF040 512KB; DIP-32_W15.24mm_Socket

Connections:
+5V: U2.1 (~MR), U2.16 (VCC), U3.7 (CEP), U3.10 (CET), U3.16 (VCC), U5.1 (~MR), U5.16 (VCC), U6.31 (~WE), U6.32 (VCC), U12.31 (~WE), U12.32 (VCC), U20.1 (~MR), U20.16 (VCC), U30.31 (~WE), U30.32 (VCC); also elsewhere on the board
/ALU/BUS0: U2.3 (D0); also elsewhere on the board
/ALU/BUS1: U2.4 (D1); also elsewhere on the board
/ALU/BUS2: U2.5 (D2); also elsewhere on the board
/ALU/BUS3: U2.6 (D3); also elsewhere on the board
/ALU/BUS4: U20.3 (D0); also elsewhere on the board
/ALU/BUS5: U20.4 (D1); also elsewhere on the board
/ALU/BUS6: U20.5 (D2); also elsewhere on the board
/ALU/BUS7: U20.6 (D3); also elsewhere on the board
/ALU/EC: U30.15 (I/O2); also elsewhere on the board
/ALU/ES: U30.14 (I/O1); also elsewhere on the board
/ALU/FLAG_C: U5.4 (D1); also elsewhere on the board
/ALU/FLAG_N: U5.5 (D2); also elsewhere on the board
/ALU/FLAG_Z: U5.3 (D0); also elsewhere on the board
/ALU/~EO: U30.13 (I/O0); also elsewhere on the board
/Control Logic/CE: U12.21 (I/O7); also elsewhere on the board
/Control Logic/Flag0: U5.14 (Q0), U6.25 (A11), U12.25 (A11), U30.25 (A11)
/Control Logic/Flag1: U5.13 (Q1), U6.4 (A12), U12.4 (A12), U30.4 (A12)
/Control Logic/Flag2: U5.12 (Q2), U6.28 (A13), U12.28 (A13), U30.28 (A13)
/Control Logic/Flag3: U5.11 (Q3), U6.29 (A14), U12.29 (A14), U30.29 (A14)
/Control Logic/Inst0: U2.14 (Q0), U6.8 (A4), U12.8 (A4), U30.8 (A4)
/Control Logic/Inst1: U2.13 (Q1), U6.7 (A5), U12.7 (A5), U30.7 (A5)
/Control Logic/Inst2: U2.12 (Q2), U6.6 (A6), U12.6 (A6), U30.6 (A6)
/Control Logic/Inst3: U2.11 (Q3), U6.5 (A7), U12.5 (A7), U30.5 (A7)
/Control Logic/Inst4: U6.27 (A8), U12.27 (A8), U20.14 (Q0), U30.27 (A8)
/Control Logic/Inst5: U6.26 (A9), U12.26 (A9), U20.13 (Q1), U30.26 (A9)
/Control Logic/Inst6: U6.23 (A10), U12.23 (A10), U20.12 (Q2), U30.23 (A10)
/Control Logic/ME: U6.13 (I/O0); also elsewhere on the board
/Control Logic/Step0: U3.14 (Q0), U6.12 (A0), U12.12 (A0), U30.12 (A0)
/Control Logic/Step1: U3.13 (Q1), U6.11 (A1), U12.11 (A1), U30.11 (A1)
/Control Logic/Step2: U3.12 (Q2), U6.10 (A2), U12.10 (A2), U30.10 (A2)
/Control Logic/Step3: U3.11 (Q3), U6.9 (A3), U12.9 (A3), U30.9 (A3)
/Control Logic/~AI: U30.19 (I/O5); also elsewhere on the board
/Control Logic/~AO: U30.20 (I/O6); also elsewhere on the board
/Control Logic/~BI: U30.17 (I/O3); also elsewhere on the board
/Control Logic/~BO: U30.18 (I/O4); also elsewhere on the board
/Control Logic/~CIH: U12.18 (I/O4); also elsewhere on the board
/Control Logic/~CIL: U12.17 (I/O3); also elsewhere on the board
/Control Logic/~COH: U12.20 (I/O6); also elsewhere on the board
/Control Logic/~COL: U12.19 (I/O5); also elsewhere on the board
/Control Logic/~FF: U6.19 (I/O5); also elsewhere on the board
/Control Logic/~FI: U5.9 (~PE), U12.14 (I/O1)
/Control Logic/~IC: U3.9 (~PE), U12.15 (I/O2)
/Control Logic/~II: U2.9 (~PE), U12.13 (I/O0), U20.9 (~PE)
/Control Logic/~MIH: U6.15 (I/O2); also elsewhere on the board
/Control Logic/~MIL: U6.14 (I/O1); also elsewhere on the board
/Control Logic/~NI: U30.21 (I/O7); also elsewhere on the board
/Control Logic/~RI: U6.20 (I/O6); also elsewhere on the board
/Control Logic/~RO: U6.21 (I/O7); also elsewhere on the board
/Control Logic/~TI: U6.17 (I/O3); also elsewhere on the board
/Control Logic/~TO: U6.18 (I/O4); also elsewhere on the board
/Control Logic/~UART_DR: U5.6 (D3); also elsewhere on the board
CLK_CTRL_AB: U2.2 (CP), U3.2 (CP), U5.2 (CP), U20.2 (CP); also elsewhere on the board
GND: U2.7 (CEP), U2.8 (GND), U2.10 (CET), U3.3 (D0), U3.4 (D1), U3.5 (D2), U3.6 (D3), U3.8 (GND), U5.7 (CEP), U5.8 (GND), U5.10 (CET), U6.1 (A18), U6.2 (A16), U6.3 (A15), U6.16 (GND), U6.22 (~CE), U6.24 (~OE), U6.30 (A17), U12.1 (A18), U12.2 (A16), U12.3 (A15), U12.16 (GND), U12.22 (~CE), U12.24 (~OE), U12.30 (A17), U20.7 (CEP), U20.8 (GND), U20.10 (CET), U30.1 (A18), U30.2 (A16), U30.3 (A15), U30.16 (GND), U30.22 (~CE), U30.24 (~OE), U30.30 (A17); also elsewhere on the board
~RESET: U3.1 (~MR); also elsewhere on the board

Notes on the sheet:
FLAGS REGISTER
INSTRUCTION REGISTER
STEP COUNTER

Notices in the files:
Legacy/Revision 1.2 (EEPROMs)/KiCAD/PC.sch:
creativecommons.org/licenses/by-nc-sa/3.0/deed.en
License: CC BY-NC-SA 3.0
Revisions 2.x (ULTRA)/Revision 2.0/KiCAD/8-Bit CPU 32k.kicad_sch:
creativecommons.org/licenses/by-nc-sa/4.0
This work is licensed under CC BY-NC-SA 4.0
